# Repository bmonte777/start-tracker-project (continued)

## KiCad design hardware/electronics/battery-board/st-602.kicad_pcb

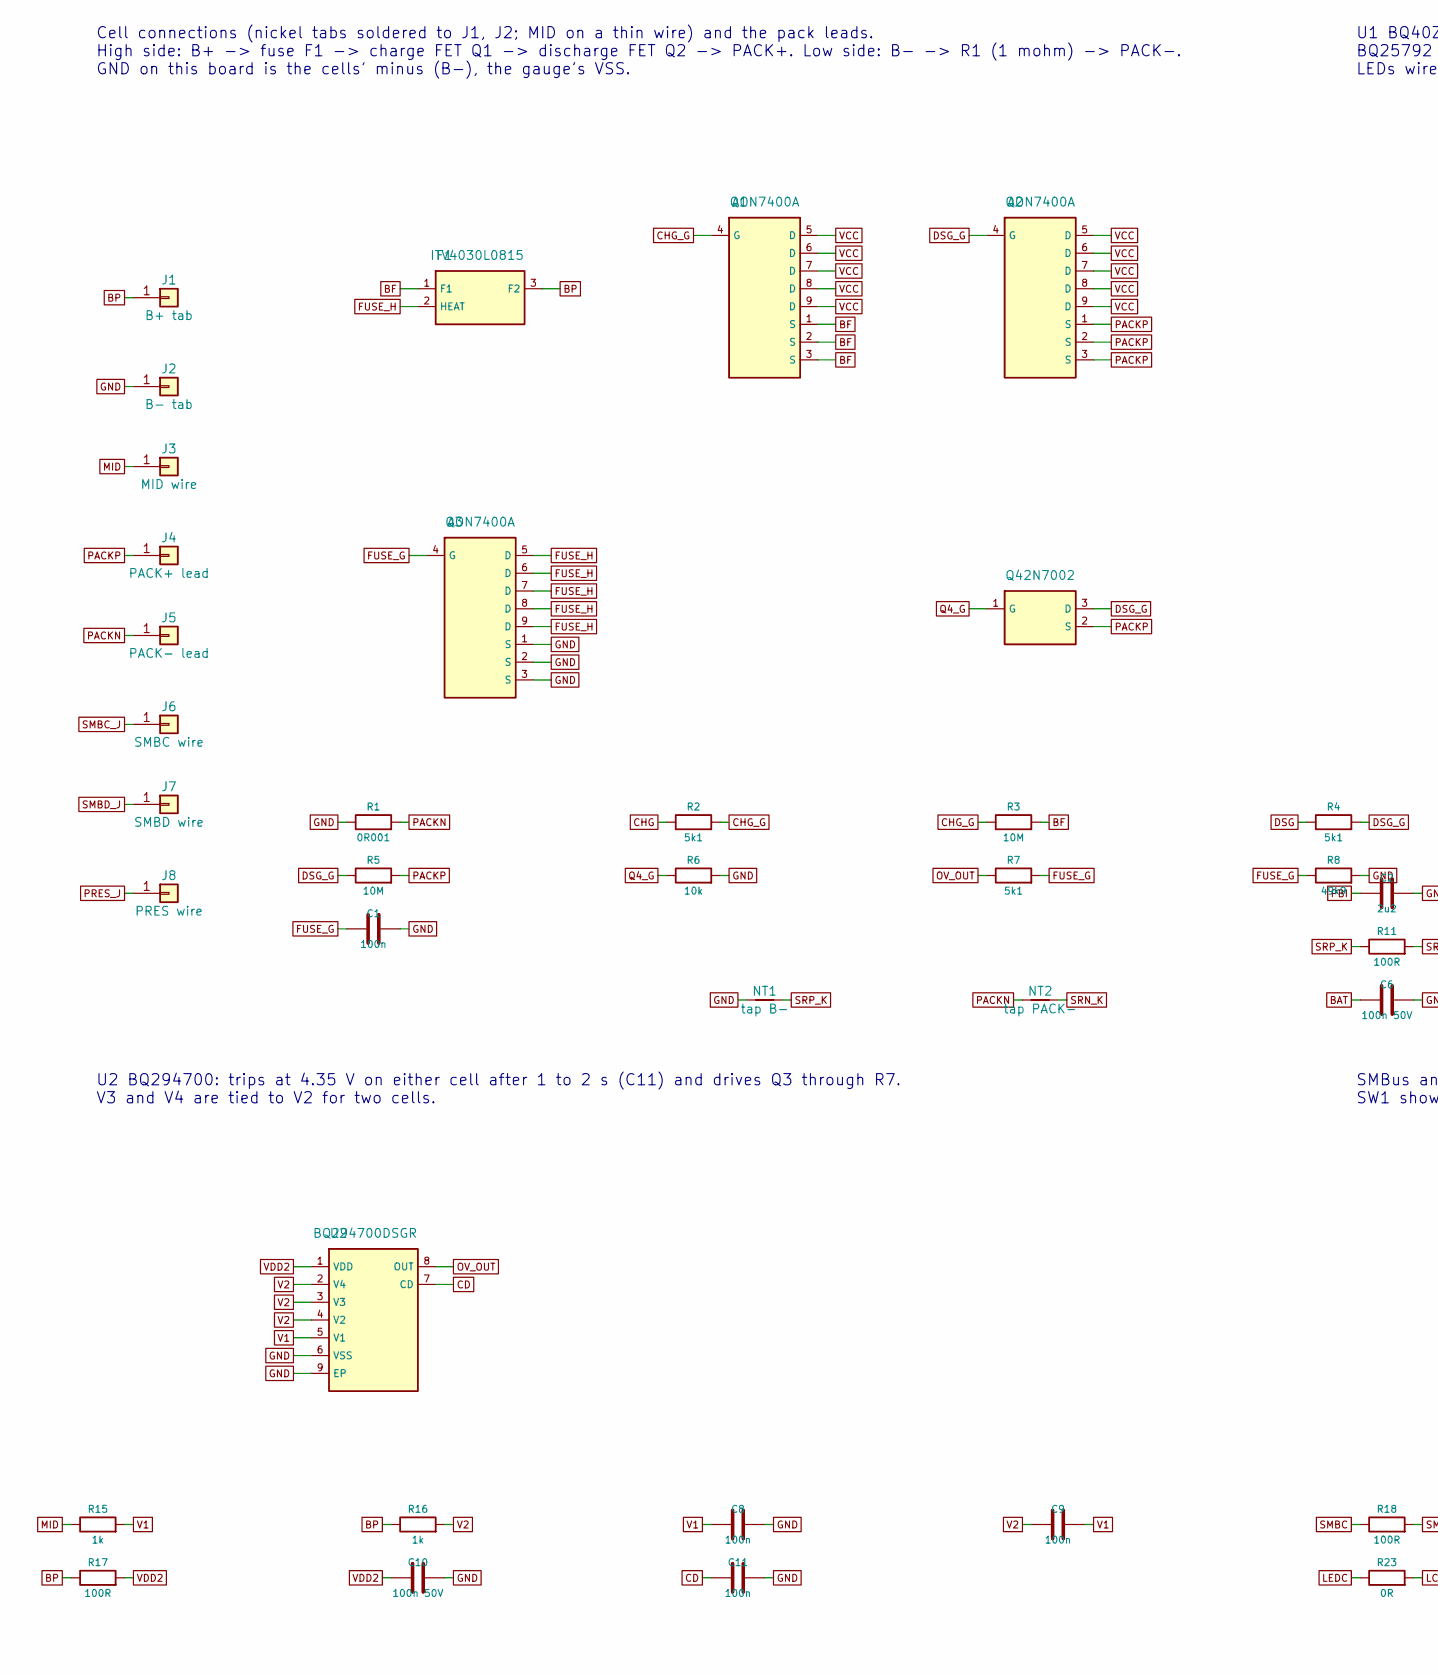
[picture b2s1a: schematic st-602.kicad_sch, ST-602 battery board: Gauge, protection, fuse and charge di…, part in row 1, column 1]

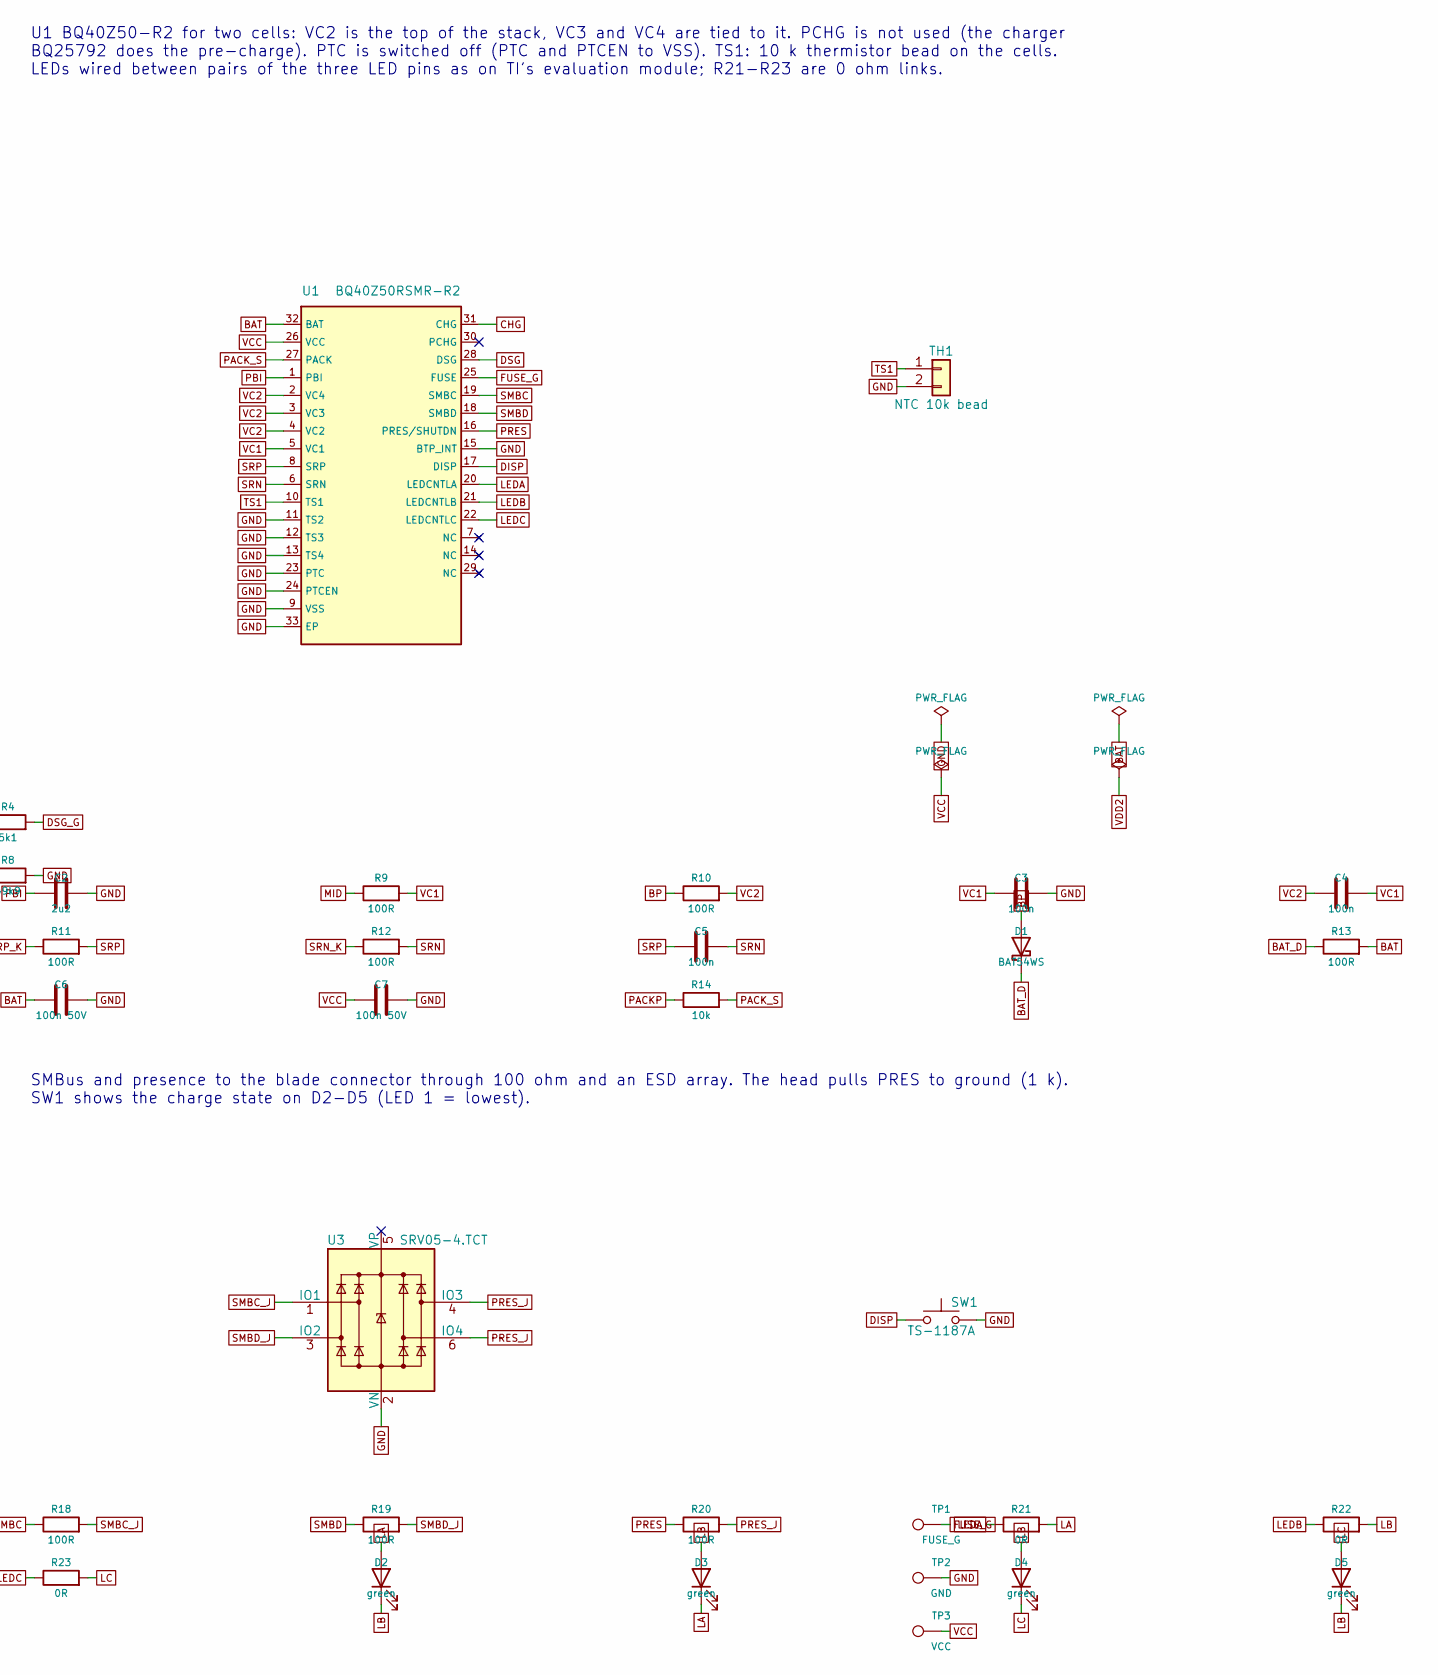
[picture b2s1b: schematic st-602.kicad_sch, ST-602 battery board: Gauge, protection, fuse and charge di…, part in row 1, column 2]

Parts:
C1, C3, C4, C5, C8, C9, C11: 100n; C_0402_1005Metric; MPN CL05B104KO5NNNC; LCSC C1525
C2: 2u2; C_0603_1608Metric; MPN CL10A225KO8NNNC; LCSC C23630
C6, C7, C10: 100n 50V; C_0402_1005Metric; MPN CL05B104KB54PNC; LCSC C307331
D1: BAT54WS; D_SOD-323; MPN BAT54WS; LCSC C2991936
D2, D3, D4, D5: green; LED_0603_1608Metric; MPN 19-217/GHC-YR1S2/3T; LCSC C72043
F1: ITV4030L0815; Fuse_Littelfuse_ITV4030; MPN ITV4030L0815NR
J1: B+ tab; TabPad_5.0x5.5mm
J2: B- tab; TabPad_5.0x5.5mm
J3: MID wire; WirePad_1.6x2.6mm
J4: PACK+ lead; WirePad_3.2x4.0mm
J5: PACK- lead; WirePad_3.2x4.0mm
J6: SMBC wire; WirePad_1.6x2.6mm
J7: SMBD wire; WirePad_1.6x2.6mm
J8: PRES wire; WirePad_1.6x2.6mm
NT1: tap B-; NetTie_2_Kelvin_0.3mm
NT2: tap PACK-; NetTie_2_Kelvin_0.3mm
Q1, Q2, Q3: AON7400A; DFN-8-1EP_3x3mm_P0.65mm_EP1.55x2.4mm; MPN AON7400A; LCSC C85734
Q4: 2N7002; SOT-23; MPN 2N7002; LCSC C8545
R1: 0R001; R_1206_3216Metric; MPN HoJLR1206-1W-1mR-1%; LCSC C2904209
R2, R4, R7: 5k1; R_0402_1005Metric; MPN 0402WGF5101TCE; LCSC C25905
R3, R5: 10M; R_0402_1005Metric; MPN 0402WGJ0106TCE; LCSC C26086
R6, R14: 10k; R_0402_1005Metric; MPN 0402WGF1002TCE; LCSC C25744
R8: 49k9; R_0402_1005Metric; MPN 0402WGF4992TCE; LCSC C25897
R9, R10, R11, R12, R13, R17, R18, R19, R20: 100R; R_0402_1005Metric; MPN 0402WGF1000TCE; LCSC C25076
R15, R16: 1k; R_0402_1005Metric; MPN 0402WGF1001TCE; LCSC C11702
R21, R22, R23: 0R; R_0402_1005Metric; MPN 0402WGF0000TCE; LCSC C17168
SW1: TS-1187A; SW_Push_1P1T_XKB_TS-1187A; MPN TS-1187A-B-A-B; LCSC C318884
TH1: NTC 10k bead; WirePads_1x02_P2.0mm_1.5x2.4mm
TP1: FUSE_G; TestPoint_Pad_D1.0mm
TP2: GND; TestPoint_Pad_D1.0mm
TP3: VCC; TestPoint_Pad_D1.0mm
U1: BQ40Z50RSMR-R2; VQFN-32-1EP_4x4mm_P0.4mm_EP2.8x2.8mm; MPN BQ40Z50RSMR-R2; LCSC C2845123
U2: BQ294700DSGR; WSON-8-1EP_2x2mm_P0.5mm_EP0.9x1.6mm; MPN BQ294700DSGR; LCSC C414622
U3: SRV05-4.TCT; SOT-23-6; MPN SRV05-4.TCT; LCSC C2687126

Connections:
BAT: C6.1, R13.2, U1.32 (BAT)
BAT_D: D1.1 (K), R13.1
BF: F1.1 (F1), Q1.1 (S), Q1.2 (S), Q1.3 (S), R3.2
BP: D1.2 (A), F1.3 (F2), J1.1, R10.1, R16.1, R17.1
CD: C11.1, U2.7 (CD)
CHG: R2.1, U1.31 (CHG)
CHG_G: Q1.4 (G), R2.2, R3.1
DISP: SW1.1, U1.17 (DISP)
DSG: R4.1, U1.28 (DSG)
DSG_G: Q2.4 (G), Q4.3 (D), R4.2, R5.1
FUSE_G: C1.1, Q3.4 (G), R7.2, R8.1, TP1.1, U1.25 (FUSE)
FUSE_H: F1.2 (HEAT), Q3.5 (D), Q3.6 (D), Q3.7 (D), Q3.8 (D), Q3.9 (D)
GND: C1.2, C2.2, C3.2, C6.2, C7.2, C8.2, C10.2, C11.2, J2.1, NT1.1, Q3.1 (S), Q3.2 (S), Q3.3 (S), R1.1, R6.2, R8.2, SW1.2, TH1.2, TP2.1, U1.9 (VSS), U1.11 (TS2), U1.12 (TS3), U1.13 (TS4), U1.15 (BTP_INT), U1.23 (PTC), U1.24 (PTCEN), U1.33 (EP), U2.6 (VSS), U2.9 (EP), U3.2 (VN)
LA: D2.2 (A), D3.1 (K), R21.2
LB: D2.1 (K), D3.2 (A), D4.2 (A), D5.1 (K), R22.2
LC: D4.1 (K), D5.2 (A), R23.2
LEDA: R21.1, U1.20 (LEDCNTLA)
LEDB: R22.1, U1.21 (LEDCNTLB)
LEDC: R23.1, U1.22 (LEDCNTLC)
MID: J3.1, R9.1, R15.1
OV_OUT: R7.1, U2.8 (OUT)
PACKN: J5.1, NT2.1, R1.2
PACKP: J4.1, Q2.1 (S), Q2.2 (S), Q2.3 (S), Q4.2 (S), R5.2, R14.1
PACK_S: R14.2, U1.27 (PACK)
PBI: C2.1, U1.1 (PBI)
PRES: R20.1, U1.16 (PRES/SHUTDN)
PRES_J: J8.1, R20.2, U3.4 (IO3), U3.6 (IO4)
Q4_G: Q4.1 (G), R6.1
SMBC: R18.1, U1.19 (SMBC)
SMBC_J: J6.1, R18.2, U3.1 (IO1)
SMBD: R19.1, U1.18 (SMBD)
SMBD_J: J7.1, R19.2, U3.3 (IO2)
SRN: C5.2, R12.2, U1.6 (SRN)
SRN_K: NT2.2, R12.1
SRP: C5.1, R11.2, U1.8 (SRP)
SRP_K: NT1.2, R11.1
TS1: TH1.1, U1.10 (TS1)
V1: C8.1, C9.2, R15.2, U2.5 (V1)
V2: C9.1, R16.2, U2.2 (V4), U2.3 (V3), U2.4 (V2)
VC1: C3.1, C4.2, R9.2, U1.5 (VC1)
VC2: C4.1, R10.2, U1.2 (VC4), U1.3 (VC3), U1.4 (VC2)
VCC: C7.1, Q1.5 (D), Q1.6 (D), Q1.7 (D), Q1.8 (D), Q1.9 (D), Q2.5 (D), Q2.6 (D), Q2.7 (D), Q2.8 (D), Q2.9 (D), TP3.1, U1.26 (VCC)
VDD2: C10.1, R17.2, U2.1 (VDD)

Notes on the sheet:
Cell connections (nickel tabs soldered to J1, J2; MID on a thin wire) and the pack leads. High side: B+ -> fuse F1 -> charge FET Q1 -> discharge FET Q2 -> PACK+. Low side: B- -> R1 (1 mohm) -> PACK-. GND on this board is the cells' minus (B-), the gauge's VSS.
U1 BQ40Z50-R2 for two cells: VC2 is the top of the stack, VC3 and VC4 are tied to it. PCHG is not used (the charger BQ25792 does the pre-charge). PTC is switched off (PTC and PTCEN to VSS). TS1: 10 k thermistor bead on the cells. LEDs wired between pairs of the three LED pins as on TI's evaluation 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
U2 BQ294700: trips at 4.35 V on either cell after 1 to 2 s (C11) and drives Q3 through R7. V3 and V4 are tied to V2 for two cells.
SMBus and presence to the blade connector through 100 ohm and an ESD array. The head pulls PRES to ground (1 k). SW1 shows the charge state on D2-D5 (LED 1 = lowest).

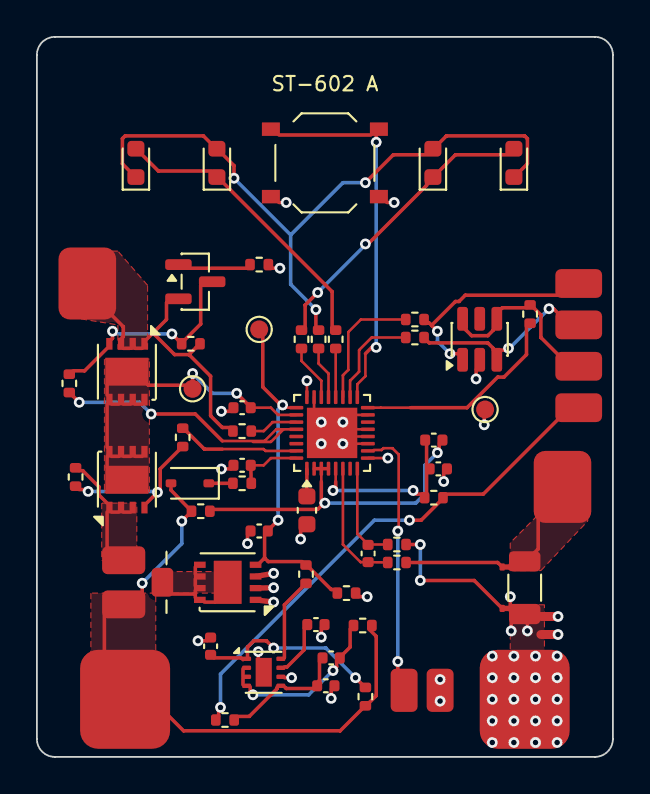
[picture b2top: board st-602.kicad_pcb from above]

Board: 2 copper layers, 32.0 x 40.0 mm, 62 parts (0 on the bottom side), 43 nets.

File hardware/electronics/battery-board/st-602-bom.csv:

Comment,Designator,Footprint,LCSC Part #,MPN,Qty
100n,"C1,C3,C4,C5,C8,C9,C11",C_0402_1005Metric,C1525,CL05B104KO5NNNC,7
2u2,C2,C_0603_1608Metric,C23630,CL10A225KO8NNNC,1
100n 50V,"C6,C7,C10",C_0402_1005Metric,C307331,CL05B104KB54PNC,3
BAT54WS,D1,D_SOD-323,C2991936,BAT54WS,1
green,"D2,D3,D4,D5",LED_0603_1608Metric,C72043,19-217/GHC-YR1S2/3T,4
ITV4030L0815,F1,Fuse_Littelfuse_ITV4030,,ITV4030L0815NR,1
AON7400A,"Q1,Q2,Q3",DFN-8-1EP_3x3mm_P0.65mm_EP1.55x2.4mm,C85734,AON7400A,3
2N7002,Q4,SOT-23,C8545,2N7002,1
0R001,R1,R_1206_3216Metric,C2904209,HoJLR1206-1W-1mR-1%,1
5k1,"R2,R4",R_0402_1005Metric,C25905,0402WGF5101TCE,2
10M,"R3,R5",R_0402_1005Metric,C26086,0402WGJ0106TCE,2
10k,"R6,R7,R14",R_0402_1005Metric,C25744,0402WGF1002TCE,3
100k,R8,R_0402_1005Metric,C25741,0402WGF1003TCE,1
100R,"R9,R10,R11,R12,R13,R17,R18,R19,R20,R21,R22,R23",R_0402_1005Metric,C25076,0402WGF1000TCE,12
1k,"R15,R16",R_0402_1005Metric,C11702,0402WGF1001TCE,2
TS-1187A,SW1,SW_Push_1P1T_XKB_TS-1187A,C318884,TS-1187A-B-A-B,1
BQ40Z50RSMR-R2,U1,VQFN-32-1EP_4x4mm_P0.4mm_EP2.8x2.8mm,C2845123,BQ40Z50RSMR-R2,1
BQ294700DSGR,U2,WSON-8-1EP_2x2mm_P0.5mm_EP0.9x1.6mm,C414622,BQ294700DSGR,1
SRV05-4.TCT,U3,SOT-23-6,C2687126,SRV05-4.TCT,1

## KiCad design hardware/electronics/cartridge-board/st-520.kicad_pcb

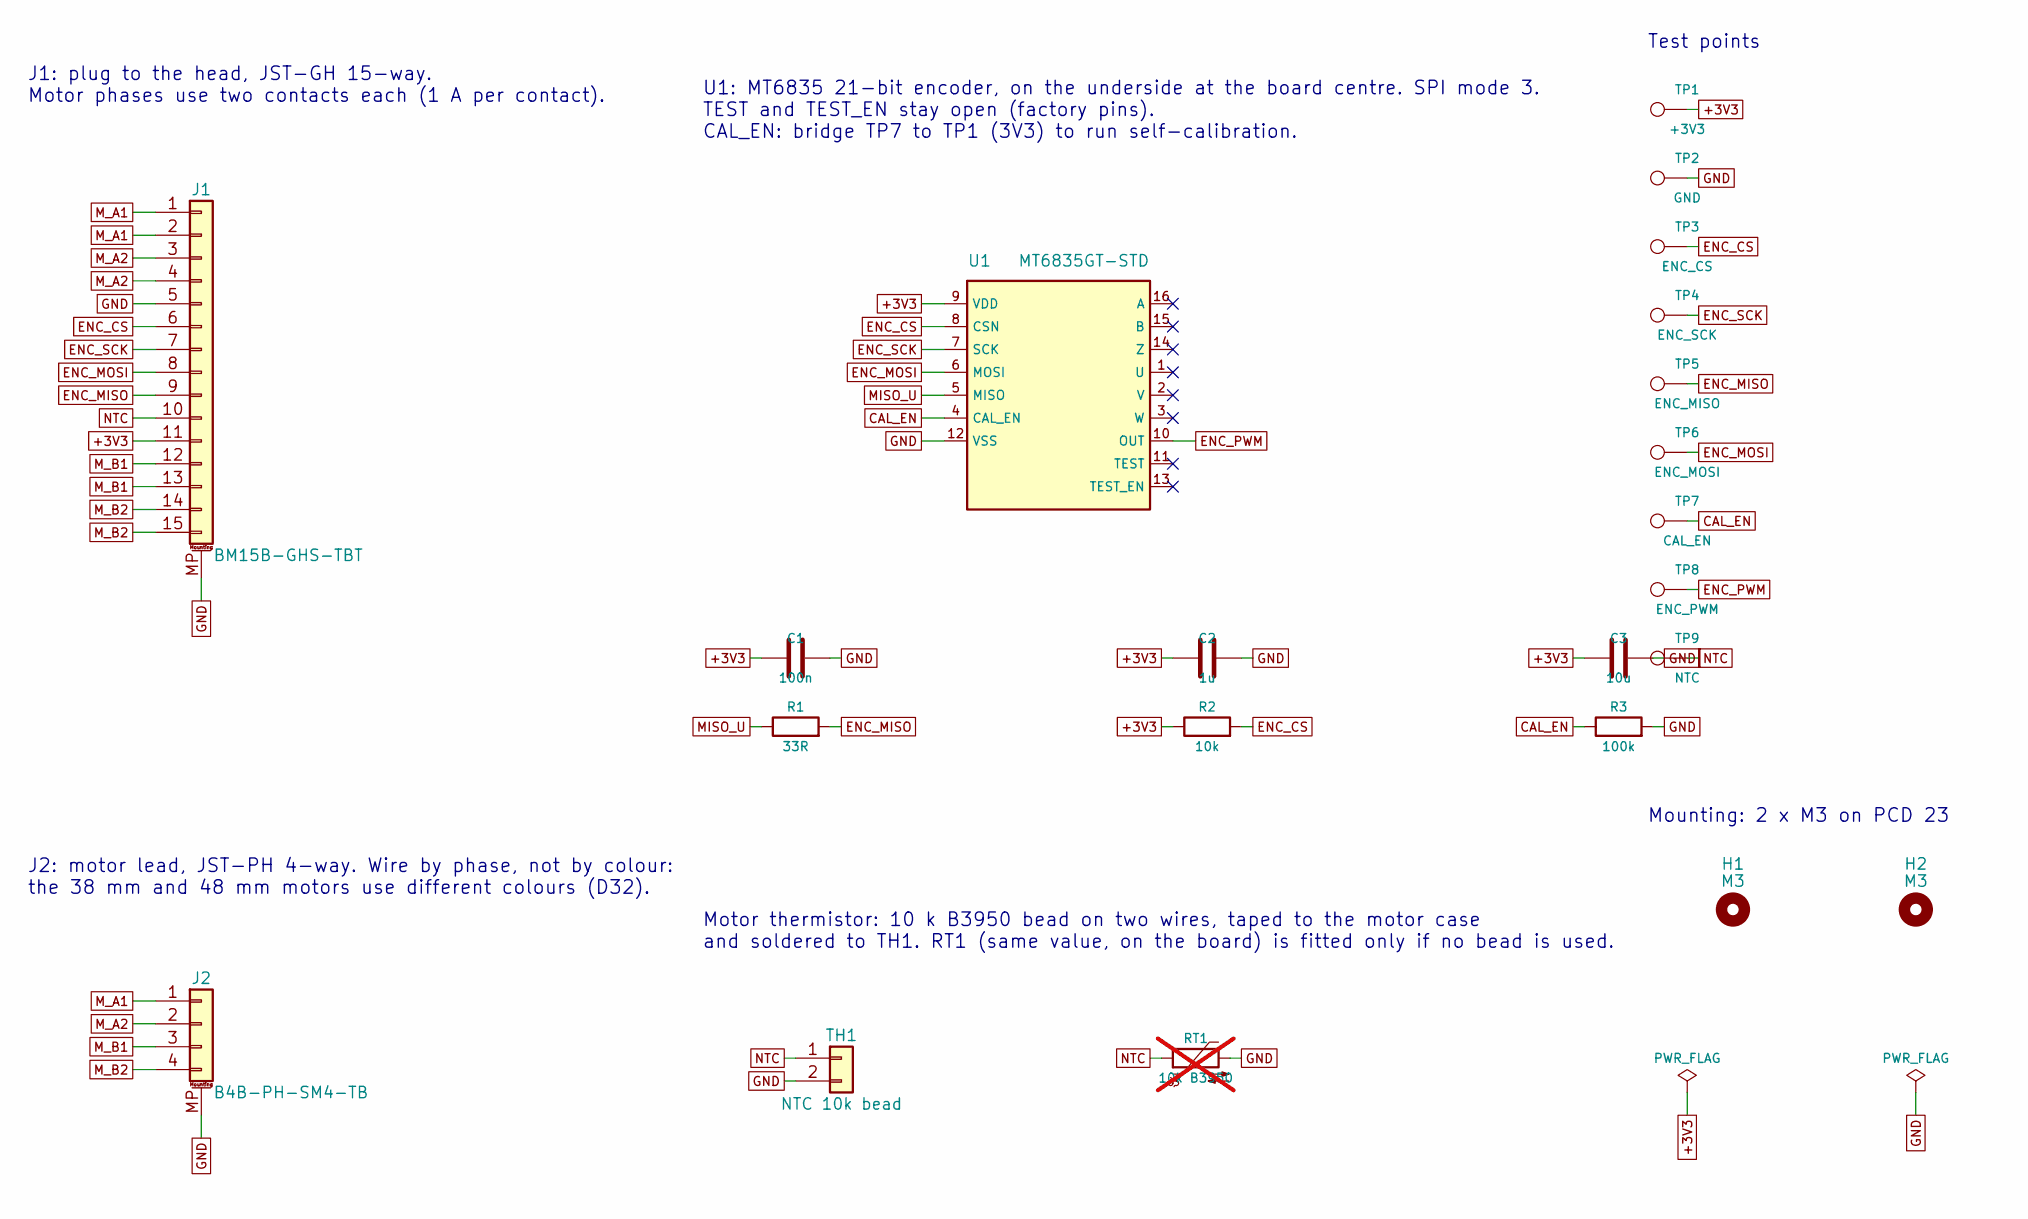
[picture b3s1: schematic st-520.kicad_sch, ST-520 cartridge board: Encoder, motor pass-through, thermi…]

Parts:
C1: 100n; C_0402_1005Metric; LCSC C1525
C2: 1u; C_0402_1005Metric; LCSC C52923
C3: 10u; C_0603_1608Metric; LCSC C19702
H1, H2: M3; MountingHole_3.2mm_M3_ISO7380
J1: BM15B-GHS-TBT; JST_GH_BM15B-GHS-TBT_1x15-1MP_P1.25mm_Vertical_3D; MPN BM15B-GHS-TBT(LF)(SN); LCSC C5305069
J2: B4B-PH-SM4-TB; JST_PH_B4B-PH-SM4-TB_1x04-1MP_P2.00mm_Vertical_3D; MPN B4B-PH-SM4-TB(LF)(SN); LCSC C160354
R1: 33R; R_0402_1005Metric; LCSC C25105
R2: 10k; R_0402_1005Metric; LCSC C25744
R3: 100k; R_0402_1005Metric; LCSC C25741
RT1: 10k B3950; R_0603_1608Metric; LCSC C13564; not fitted
TH1: NTC 10k bead; WirePads_1x02_P2.0mm_1.5x2.4mm
TP1: +3V3; TestPoint_Pad_D1.0mm
TP2: GND; TestPoint_Pad_D1.0mm
TP3: ENC_CS; TestPoint_Pad_D1.0mm
TP4: ENC_SCK; TestPoint_Pad_D1.0mm
TP5: ENC_MISO; TestPoint_Pad_D1.0mm
TP6: ENC_MOSI; TestPoint_Pad_D1.0mm
TP7: CAL_EN; TestPoint_Pad_D1.0mm
TP8: ENC_PWM; TestPoint_Pad_D1.0mm
TP9: NTC; TestPoint_Pad_D1.0mm
U1: MT6835GT-STD; TSSOP-16_4.4x5mm_P0.65mm; MPN MT6835GT-STD; LCSC C2984637

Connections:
+3V3: C1.1, C2.1, C3.1, J1.11, R2.1, TP1.1, U1.9 (VDD)
CAL_EN: R3.1, TP7.1, U1.4 (CAL_EN)
ENC_CS: J1.6, R2.2, TP3.1, U1.8 (CSN)
ENC_MISO: J1.9, R1.2, TP5.1
ENC_MOSI: J1.8, TP6.1, U1.6 (MOSI)
ENC_PWM: TP8.1, U1.10 (OUT)
ENC_SCK: J1.7, TP4.1, U1.7 (SCK)
GND: C1.2, C2.2, C3.2, J1.5, J1.MP (MountPin), J2.MP (MountPin), R3.2, RT1.2, TH1.2, TP2.1, U1.12 (VSS)
MISO_U: R1.1, U1.5 (MISO)
M_A1: J1.1, J1.2, J2.1
M_A2: J1.3, J1.4, J2.2
M_B1: J1.12, J1.13, J2.3
M_B2: J1.14, J1.15, J2.4
NTC: J1.10, RT1.1, TH1.1, TP9.1

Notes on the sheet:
J1: plug to the head, JST-GH 15-way. Motor phases use two contacts each (1 A per contact).
J2: motor lead, JST-PH 4-way. Wire by phase, not by colour: the 38 mm and 48 mm motors use different colours (D32).
U1: MT6835 21-bit encoder, on the underside at the board centre. SPI mode 3. TEST and TEST_EN stay open (factory pins). CAL_EN: bridge TP7 to TP1 (3V3) to run self-calibration.
Motor thermistor: 10 k B3950 bead on two wires, taped to the motor case and soldered to TH1. RT1 (same value, on the board) is fitted only if no bead is used.
Test points
Mounting: 2 x M3 on PCD 23

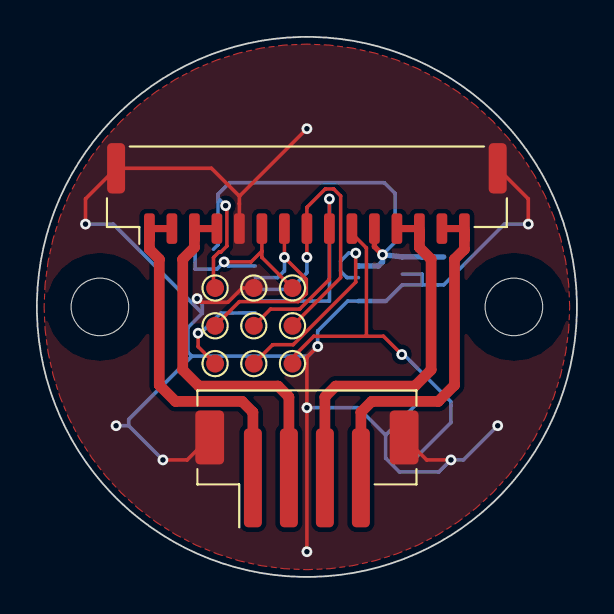
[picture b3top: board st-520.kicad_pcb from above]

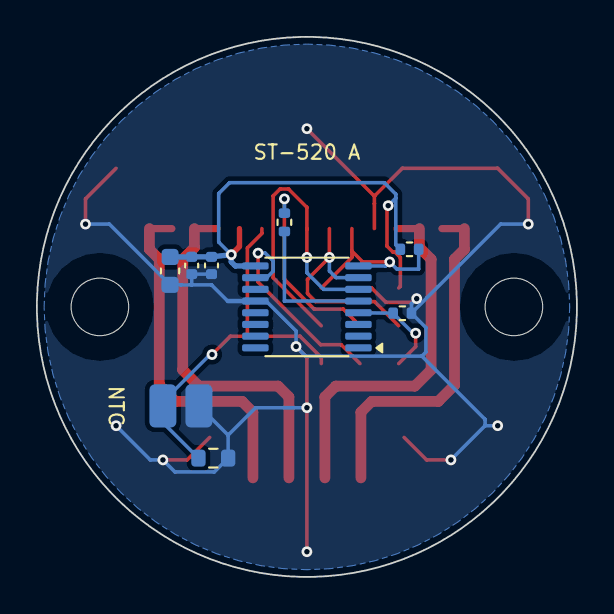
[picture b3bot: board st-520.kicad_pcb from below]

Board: 2 copper layers, 30.0 x 30.0 mm, 22 parts (9 on the bottom side), 14 nets.

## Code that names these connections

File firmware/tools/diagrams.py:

#!/usr/bin/env python3
"""Draw the Phase 5 firmware diagrams (Graphviz) into docs/img/05-*.svg and .png."""
import pathlib
import subprocess

OUT = pathlib.Path(__file__).resolve().parents[2] / "docs/img"
FONT = 'fontname="Helvetica"'
BASE = f'graph [{FONT} fontsize=11 bgcolor=white pad=0.2]; node [{FONT} fontsize=10 shape=box style="rounded,filled" fillcolor="#f4f6fa" color="#4a5a75"]; edge [{FONT} fontsize=9 color="#4a5a75"];'

DIAGRAMS = {
"05-firmware-overview": f"""
digraph G {{ {BASE} rankdir=LR; compound=true; newrank=true;
 subgraph cluster_app {{ label="ESP32-S3 — application (ESP-IDF 5.5, C++17)"; style="rounded"; color="#2f6db5";
   subgraph cluster_c0 {{ label="core 0: radio and network"; style=dashed;
     wifi [label="Wi-Fi STA / AP\\nmDNS startracker.local"]; ble [label="BLE set-up\\n(NimBLE GATT)"];
     http [label="HTTP :80 / :32323\\nAlpaca Telescope + Rotator\\nweb UI, /api/update"]; ws [label="WebSocket /ws/v1\\nJSON API (apps)"];
     lx [label="LX200 TCP :4030"]; disc [label="Alpaca discovery\\nUDP 32227"]; }}
   subgraph cluster_c1 {{ label="core 1: head logic"; style=dashed;
     head [label="Head model\\n(state, settings, faults)" fillcolor="#e3ecf9"];
     trk [label="tracker 10 Hz\\nastro · kinematics · pointing\\nPEC · jobs"]; pwr [label="power 2 Hz\\nPD A/B · charger · gauge\\npack budget · sleep"];
     sens [label="sensors\\nGNSS · RTC · IMU · mag"]; ui [label="UI 10 Hz\\nOLED · 4 buttons · 3 LEDs"];
     shut [label="shutter / intervalometer\\n(esp_timer)"]; lnk [label="link task\\nCOBS frames · time sync"];
     sys [label="system\\nOTA · SWD flasher · NVS"]; }}
 }}
 subgraph cluster_mot {{ label="RP2354A — motion (Pico SDK 2.3, C11)"; style="rounded"; color="#b5602f";
   c0 [label="core 0\\nlink · encoders 1 kHz (SPI1)\\ncorrection loop 5 Hz · drivers UART\\nsafety · ADC · watchdog"];
   c1 [label="core 1\\nmotion tick 1 kHz\\nprofiles · tracking · PEC\\nstep planning" fillcolor="#fbeee4"];
   pio [label="PIO0: 3 step generators\\nPIO1: PPS / SYNC timestamps"];
 }}
 hw1 [label="3 × TMC2209\\n(UART addr 0,1,2)" shape=component]; hw2 [label="3 × MT6835\\n(SPI, 3 CS)" shape=component];
 hw3 [label="motor rail\\nsoft start · boost 10/16 V" shape=component];
 hw4 [label="TPS25751 / TPS25752\\nBQ40Z50 · sensors · OLED" shape=component];
 apps [label="apps (Phase 6)\\nN.I.N.A., Stellarium, SkySafari" shape=note fillcolor="#fff8dc"];
 apps -> http; apps -> ws; apps -> lx; apps -> ble;
 http -> head; ws -> head; lx -> head; ble -> head; head -> trk; trk -> lnk; pwr -> lnk [label="budget"]; sens -> trk; ui -> head; head -> ui;
 lnk -> c0 [label="UART 921 600 bd\\nLINK_SYNC · 1 PPS" dir=both color="#b5602f" penwidth=1.6];
 c0 -> c1 [label="setpoints,\\nencoder data" dir=both]; c1 -> pio; pio -> hw1 [label="STEP/DIR"]; c0 -> hw1 [label="UART"]; c0 -> hw2; c0 -> hw3; pwr -> hw4; sens -> hw4; ui -> hw4;
 sys -> c0 [label="SWD (IO38/39)\\nRUN (IO40)" style=dashed];
}}""",

"05-rp2354a-timing": f"""
digraph G {{ {BASE} rankdir=TB;
 tick [label="1 kHz alarm (core 1)\\n= motion tick, budget 1000 µs" fillcolor="#fbeee4"];
 a [label="read encoder snapshot (seqlock)\\nread commanded mode per axis  ≈ 3 µs"];
 b [label="per axis: target angle at tick end\\nS-curve / setpoint polynomial + PEC + correction  ≈ 10 µs × 3"];
 c [label="angle → microsteps (×15 360 000 / 2^32)\\nlimit clamp, max 400 steps per tick"];
 d [label="push segment to PIO FIFO\\n(dir | count, half-period)  ≈ 1 µs × 3"];
 e [label="publish state (seqlock)\\ntotal ≈ 45 µs = 4.5 % of core 1" fillcolor="#e3f3e3"];
 tick -> a -> b -> c -> d -> e;
 c0 [label="core 0 main loop" fillcolor="#e3ecf9"]; f [label="every 1 ms: burst-read 3 × MT6835\\n(48 bits @ 8 MHz, ≈ 25 µs)"];
 g [label="every 10 ms: ADC (3 NTC + VMOT), STATE frame,\\nfault checks"]; h [label="every 100 ms: TMC2209 DRV_STATUS / SG_RESULT\\n(1 driver per 33 ms)"];
 i [label="every 200 ms: encoder correction + slip check"]; j [label="link RX (UART IRQ → ring) · watchdog feed"];
 c0 -> f; c0 -> g; c0 -> h; c0 -> i; c0 -> j;
}}""",

"05-system-states": f"""
digraph G {{ {BASE} rankdir=LR;
 off [label="Off / deep sleep" shape=ellipse fillcolor="#e9e9e9"]; boot [label="Boot\\n(rails up, RP in reset)"]; st [label="Self-test\\nI²C, PD, gauge, link, encoders"];
 idle [label="Idle\\nmotor rail off" fillcolor="#e3f3e3"]; op [label="Operating\\nrail 10 V (16 V while slewing)\\naxes: hold · move · track" fillcolor="#e3ecf9"];
 park [label="Parking\\nroll 0°, then park pose"]; flt [label="Fault\\nramp to rest, report" fillcolor="#f8dddd"]; upd [label="Updating\\nESP32 / RP2354A"];
 off -> boot [label="button · RTC alarm · USB/PD event"]; boot -> st; st -> idle [label="pass"]; st -> flt [label="fail"];
 idle -> op [label="go-to / track / jog"]; op -> idle [label="stop + 30 s hold"]; op -> park [label="park · battery 5 % or 6.2 V (D25)"];
 park -> idle; idle -> off [label="sleep timer · power button"]; op -> flt [label="fault"]; flt -> st [label="clear (always via self-test)"];
 idle -> upd; upd -> boot [label="reboot"];
}}""",

"05-axis-states": f"""
digraph G {{ {BASE} rankdir=LR;
 dis [label="Disabled\\nDRV_EN_N high"]; hold [label="Holding\\nI_hold, StealthChop"]; mov [label="Moving\\nS-curve, 16 V, SpreadCycle above TPWMTHRS"];
 trk [label="Tracking\\nsetpoint polynomial + PEC\\nI_track, 10 V, StealthChop"]; stp [label="Stopping\\nramp to rest"]; flt [label="Fault" fillcolor="#f8dddd"];
 dis -> hold [label="rail OK, drivers set"]; hold -> mov [label="MOVE"]; mov -> hold [label="done"]; hold -> trk [label="SETPOINT"]; trk -> hold [label="STOP"];
 mov -> stp [label="STOP · limit · link lost"]; trk -> stp [label="limit · stale 60 s"]; stp -> hold; mov -> flt [label="stall · slip > 0.05°"]; trk -> flt [label="slip · 95 °C"];
 flt -> hold [label="re-sync from encoder"]; hold -> dis [label="rail off"];
}}""",

"05-power-states": f"""
digraph G {{ {BASE} rankdir=TB;
 pack [label="Pack only\\nVSYS = pack 6.0–8.4 V"]; chg [label="USB-C A sink\\ncharging (PD contract 15/20 V)"]; src [label="USB-C A source\\n(phone / camera from pack)"];
 b5 [label="Port B 5 V / 3 A"]; b9 [label="Port B 9 V / 3 A (27 W)"]; b15 [label="Port B re-advertised 15 W\\n(budget exceeded)" fillcolor="#fff3d6"];
 low [label="Low battery: 5 % or 6.2 V\\nfinish exposure → park → sleep" fillcolor="#f8dddd"];
 pack -> chg [label="charger plugged"]; chg -> pack [label="unplugged"]; pack -> src [label="sink device plugged, SoC > 20 %"]; src -> pack;
 b5 -> b9 [label="camera asks 9 V"]; b9 -> b15 [label="P_motion + P_camera > 6 A × V_pack\\nafter slew current already lowered"]; b15 -> b9 [label="slew finished"];
 pack -> low;
 rail [label="Motor rail (RP2354A)\\nMOTOR_PWR_EN → 5 ms → BOOST_EN → 10 ms → VMOT ≈ 10 V ✓ → drivers set → DRV_EN_N low\\nVM_SEL high only while slewing"];
}}""",

"05-update-flow": f"""
digraph G {{ {BASE} rankdir=TB;
 up [label=".stfw bundle uploaded\\n(head web page, app, or web flasher)"]; ver [label="check manifest + SHA-256 of both images"];
 wesp [label="write ESP32 image to the idle OTA slot"]; wrp [label="store RP2354A image in 'rp_new'"]; rb [label="reboot into new ESP32 image (pending verify)"];
 flash [label="SWD: hold RUN, write RP flash, release RUN"]; hello [label="RP HELLO within 3 s\\nand self-test passes?" shape=diamond fillcolor="#fff8dc"];
 ok [label="mark ESP32 slot valid\\nrp_new → rp_good" fillcolor="#e3f3e3"]; bad [label="reflash rp_good over SWD\\nroll ESP32 back to the old slot" fillcolor="#f8dddd"];
 up -> ver -> wesp -> wrp -> rb -> flash -> hello; hello -> ok [label="yes"]; hello -> bad [label="no"];
 note [label="Always available: ESP32 ROM loader over USB (web flasher in Chrome) and the RP2354A Debug Probe pads J6" shape=note fillcolor="#fff8dc"];
}}""",
}


def main():
    OUT.mkdir(parents=True, exist_ok=True)
    for name, src in DIAGRAMS.items():
        for fmt in ("svg", "png"):
            args = ["dot", f"-T{fmt}", "-o", str(OUT / f"{name}.{fmt}")]
            if fmt == "png":
                args.insert(1, "-Gdpi=130")
            subprocess.run(args, input=src.encode(), check=True)
        print("drew", name)


if __name__ == "__main__":
    main()

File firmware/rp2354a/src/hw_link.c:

/* Star Tracker RP2354A — link UART0 (GPIO0 TX, GPIO1 RX) at 921 600 baud, interrupt-driven receive ring. */
#include "hw.h"
#include "hardware/gpio.h"
#include "hardware/irq.h"
#include "hardware/uart.h"

#define RING 2048
static volatile uint8_t ring[RING];
static volatile uint16_t rw, rr;
static st_link_rx_t rx;
static uint8_t tx_seq;

static void uart_isr(void)
{
    while (uart_is_readable(uart0)) {
        uint8_t b = (uint8_t)uart_getc(uart0);
        uint16_t n = (uint16_t)((rw + 1) % RING);
        if (n != rr) { ring[rw] = b; rw = n; }
    }
}

void hw_link_init(st_link_frame_cb cb, void *ctx)
{
    uart_init(uart0, ST_LINK_BAUD);
    gpio_set_function(RP_GPIO_LINK_RX, GPIO_FUNC_UART);    /* net LINK_RX = RP2354A TX (GPIO0) */
    gpio_set_function(RP_GPIO_LINK_TX, GPIO_FUNC_UART);    /* net LINK_TX = RP2354A RX (GPIO1) */
    uart_set_fifo_enabled(uart0, true);
    irq_set_exclusive_handler(UART0_IRQ, uart_isr);
    irq_set_enabled(UART0_IRQ, true);
    uart_set_irq_enables(uart0, true, false);
    st_link_rx_init(&rx, cb, ctx);
}

void hw_link_poll(void)
{
    uint8_t buf[64];
    for (;;) {
        size_t n = 0;
        while (rr != rw && n < sizeof buf) { buf[n++] = ring[rr]; rr = (uint16_t)((rr + 1) % RING); }
        if (!n) break;
        st_link_rx_feed(&rx, buf, n);
    }
}

bool hw_link_send(uint8_t type, const void *payload, size_t len)
{
    uint8_t frame[ST_LINK_MAX_FRAME + 8];
    size_t n = st_link_build(type, tx_seq++, payload, len, frame);
    if (!n) return false;
    uart_write_blocking(uart0, frame, n);                  /* 260 bytes max = 2.8 ms at 921 600 */
    return true;
}

st_link_rx_t *hw_link_rx(void) { return &rx; }

void hw_led_init(void) { gpio_init(RP_GPIO_LED_RP); gpio_set_dir(RP_GPIO_LED_RP, GPIO_OUT); }
void hw_led_set(bool on) { gpio_put(RP_GPIO_LED_RP, on); }

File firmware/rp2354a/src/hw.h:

/* Star Tracker RP2354A — hardware layer. Pins come only from st_board.h (generated from the schematic). */
#pragma once
#include <stdbool.h>
#include <stdint.h>
#include "st_board.h"
#include "st_link.h"

/* ---- step generators (PIO0, stepgen.pio) ---- */
void     hw_stepgen_init(void);
bool     hw_stepgen_push(int axis, int32_t steps, uint32_t tick_us);   /* false if the FIFO was full */
uint32_t hw_stepgen_overflows(void);

/* ---- MT6835 encoders on SPI1, shared MISO, CS per axis ---- */
typedef struct { uint32_t raw; uint8_t status; bool crc_ok; } enc_sample_t;
void     hw_enc_init(uint32_t baud);
bool     hw_enc_read(int axis, enc_sample_t *s);          /* burst read 0x003..0x006 */
bool     hw_enc_reg_read(int axis, uint16_t reg, uint8_t *val);
bool     hw_enc_reg_write(int axis, uint16_t reg, uint8_t val);
uint8_t  hw_enc_crc8(const uint8_t *p, int n);

/* ---- TMC2209 drivers on UART1, one wire, addresses 0/1/2 ---- */
#define TMC_GCONF      0x00
#define TMC_GSTAT      0x01
#define TMC_IFCNT      0x02
#define TMC_SLAVECONF  0x03
#define TMC_IOIN       0x06
#define TMC_IHOLD_IRUN 0x10
#define TMC_TPOWERDOWN 0x11
#define TMC_TSTEP      0x12
#define TMC_TPWMTHRS   0x13
#define TMC_TCOOLTHRS  0x14
#define TMC_SGTHRS     0x40
#define TMC_SG_RESULT  0x41
#define TMC_COOLCONF   0x42
#define TMC_MSCNT      0x6A
#define TMC_CHOPCONF   0x6C
#define TMC_DRV_STATUS 0x6F
#define TMC_PWMCONF    0x70
#define TMC_PWM_SCALE  0x71
typedef struct { uint8_t addr; bool ok; uint16_t ma; bool vsense; uint32_t errors; } tmc_t;
void     hw_tmc_init(void);
uint8_t  hw_tmc_crc(const uint8_t *p, int n);
bool     hw_tmc_write(uint8_t addr, uint8_t reg, uint32_t val);
bool     hw_tmc_read(uint8_t addr, uint8_t reg, uint32_t *val);
bool     hw_tmc_setup(int axis);                          /* full register set-up, verified */
bool     hw_tmc_set_current(int axis, uint16_t ma);       /* picks vsense and CS */
bool     hw_tmc_set_spread_above(int axis, float dps, double usteps_per_rev);
bool     hw_tmc_set_stall(int axis, uint8_t sgthrs, float min_dps, double usteps_per_rev);
void     hw_tmc_enable(bool on);                          /* DRV_EN_N */
bool     hw_tmc_diag(int axis);
extern tmc_t hw_tmc[ST_AXES];

/* ---- motor rail (D43, D45, Phase 4 section 10.5) and ADC ---- */
typedef enum { RAIL_OFF = 0, RAIL_10V = 1, RAIL_16V = 2 } rail_level_t;
void     hw_rail_init(void);
bool     hw_rail_set(rail_level_t lvl);                   /* runs the soft-start sequence; checks VMOT */
rail_level_t hw_rail_get(void);
float    hw_adc_volts(int ch);                            /* ch 0..3 = GPIO26..29 */
float    hw_vmot(void);
float    hw_ntc_c(int axis);
float    hw_ntc_from_volts(float v);

/* ---- time base: 1 PPS (GPIO3) and LINK_SYNC (GPIO2) edges ---- */
void     hw_time_init(void);
uint64_t hw_head_us(void);                                /* head time now */
uint64_t hw_head_from_local(uint64_t local_us);
void     hw_time_on_timesync(const st_timesync_t *ts);    /* pairs the last LINK_SYNC edge with its head time */
double   hw_time_ppm(void);                               /* crystal error measured on PPS */
uint32_t hw_time_pps_count(void);

/* ---- link UART0 ---- */
void     hw_link_init(st_link_frame_cb cb, void *ctx);
void     hw_link_poll(void);                              /* drain the RX ring into the frame decoder */
bool     hw_link_send(uint8_t type, const void *payload, size_t len);
st_link_rx_t *hw_link_rx(void);

/* ---- heartbeat LED ---- */
void     hw_led_init(void);
void     hw_led_set(bool on);
